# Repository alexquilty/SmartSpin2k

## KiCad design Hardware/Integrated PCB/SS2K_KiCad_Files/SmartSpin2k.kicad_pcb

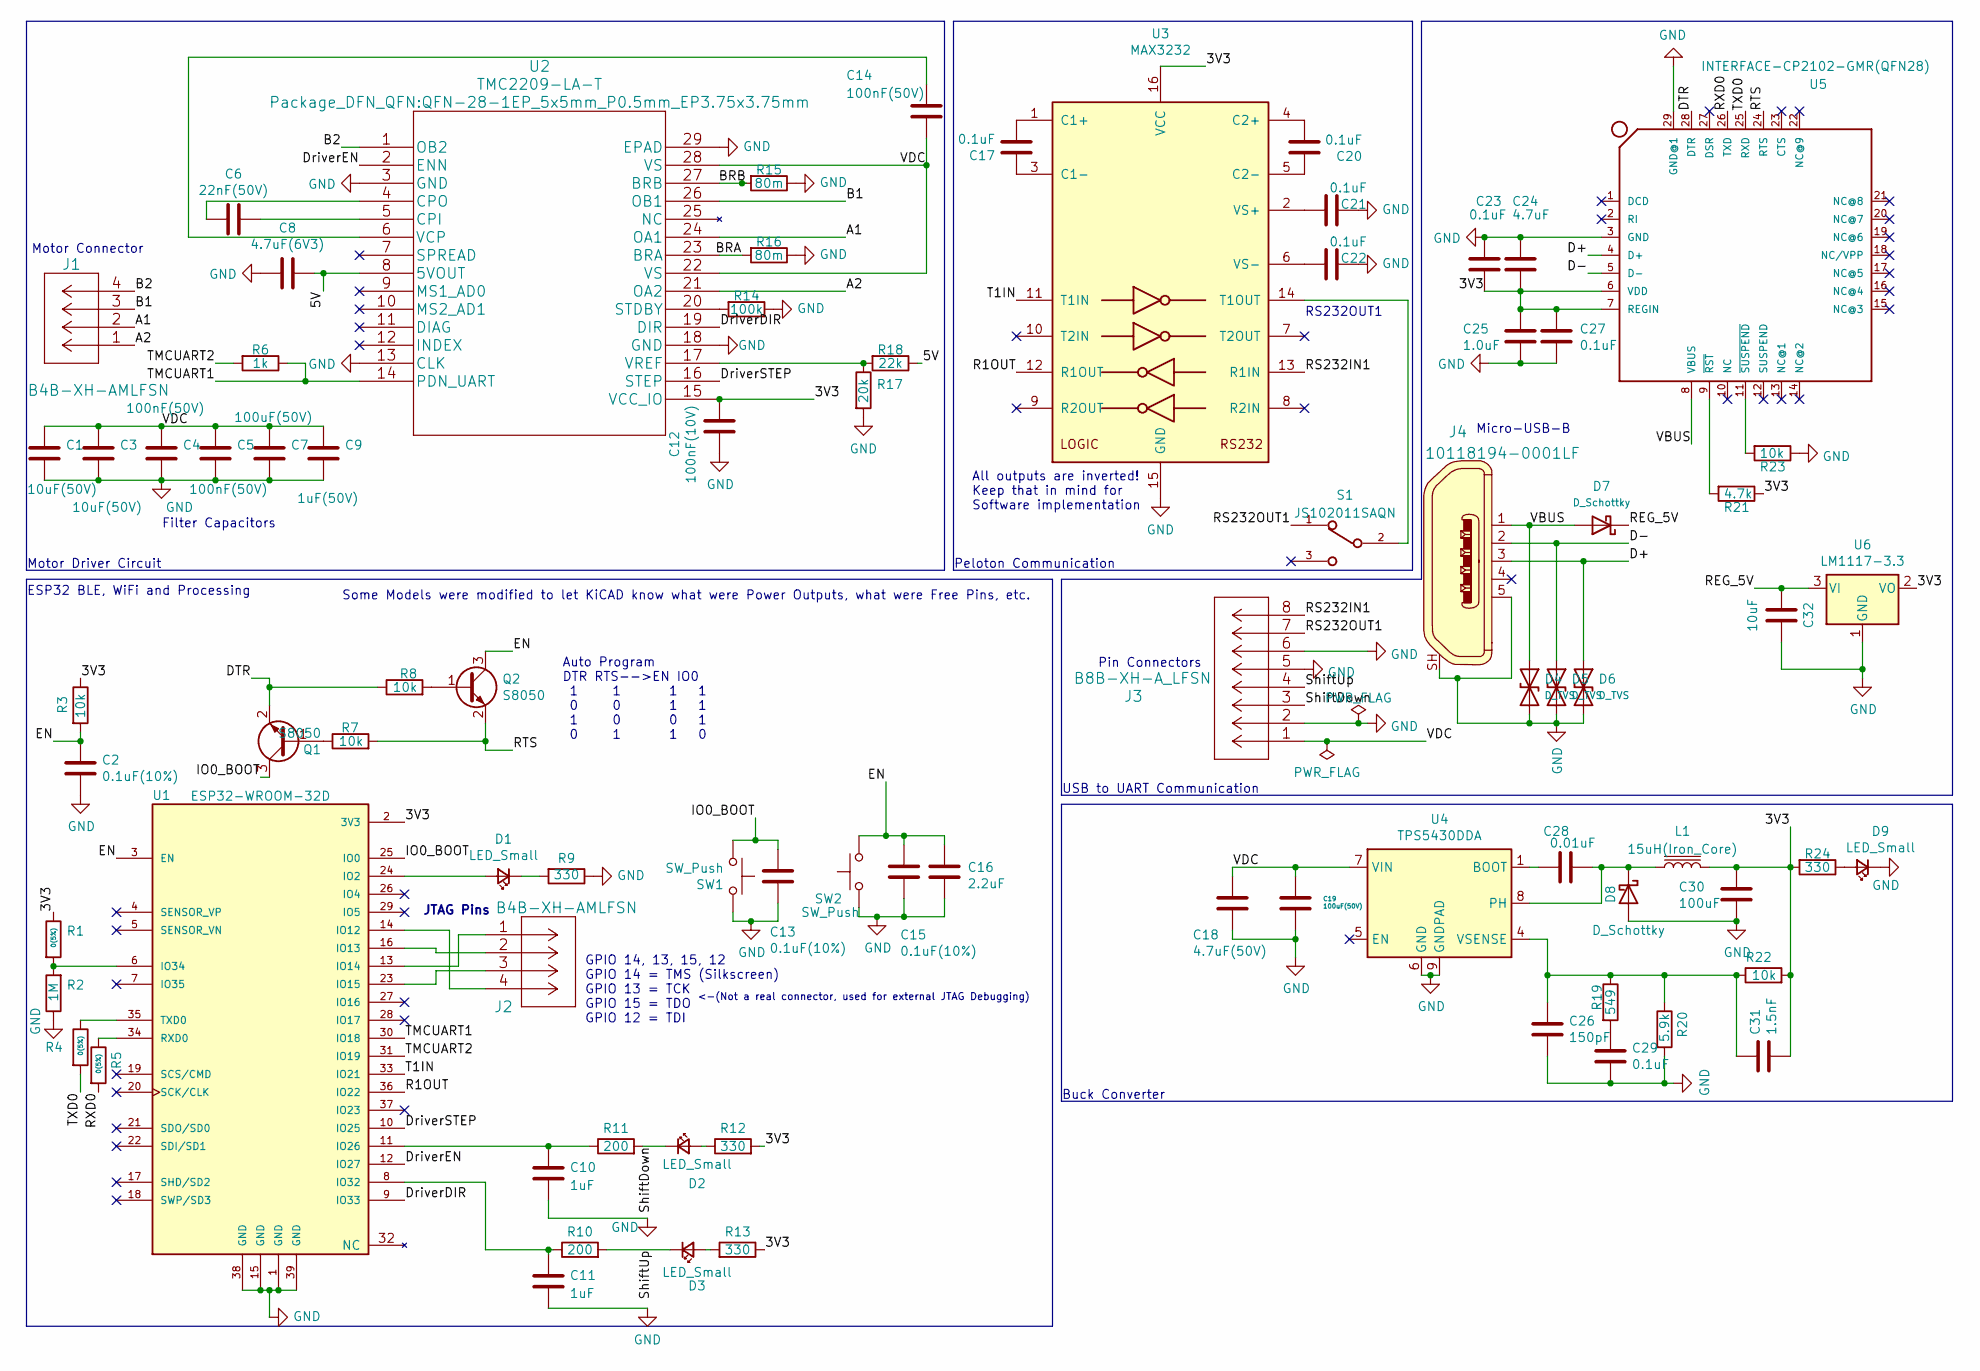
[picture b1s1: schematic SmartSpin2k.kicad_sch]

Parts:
C1: 10uF(50V); C_0805_2012Metric
C2, C13, C15: 0.1uF(10%); C_0402_1005Metric
C3: 10uF(50V); C_1206_3216Metric
C4, C5, C14: 100nF(50V); C_0805_2012Metric
C6: 22nF(50V); C_0805_2012Metric
C7, C19: 100uF(50V); CP_Elec_8x10
C8: 4.7uF(6V3); C_0805_2012Metric
C9: 1uF(50V); C_0603_1608Metric
C10, C11: 1uF; C_0603_1608Metric
C12: 100nF(10V); C_0805_2012Metric
C16: 2.2uF; C_0402_1005Metric
C17, C20, C21, C22, C23, C27, C29: 0.1uF; C_0402_1005Metric
C18: 4.7uF(50V); C_1206_3216Metric
C24: 4.7uF; C_0805_2012Metric
C25: 1.0uF; C_0805_2012Metric
C26: 150pF; C_0805_2012Metric
C28: 0.01uF; C_0805_2012Metric
C30: 100uF; C_1206_3216Metric
C31: 1.5nF; C_0805_2012Metric
C32: 10uF; C_0603_1608Metric
D1, D2, D3, D9: LED_Small; LED_0603_1608Metric
D4, D5, D6: D_TVS; D_0603_1608Metric
D7, D8: D_Schottky; D_SMA
J1, J2: B4B-XH-AMLFSN; JST_XH_B4B-XH-AM_1x04_P2.50mm_Vertical
J3: B8B-XH-A_LFSN; JST_XH_B8B-XH-AM_1x08_P2.50mm_Vertical
J4: 10118194-0001LF; USB_Micro_B_Female_10118194-0001LF; MPN 10118194-0001LF; Digi-Key_PN 609-4618-1-ND
L1: 15uH(Iron_Core); L_SXN_SMDRI127_150MT
Q1, Q2: S8050; SOT-23
R1, R4, R5: 0(5%); R_0402_1005Metric
R2: 1M; R_0402_1005Metric
R3, R7, R8, R22, R23: 10k; R_0402_1005Metric
R6: 1k; R_0402_1005Metric
R9, R12, R13, R24: 330; R_0402_1005Metric
R10, R11: 200; R_0402_1005Metric
R14: 100k; R_0402_1005Metric
R15, R16: 80m; R_1206_3216Metric
R17: 20k; R_0805_2012Metric
R18: 22k; R_0402_1005Metric
R19: 549; R_0402_1005Metric
R20: 5.9k; R_0603_1608Metric
R21: 4.7k; R_0402_1005Metric
S1: JS102011SAQN; SW_JS102011SAQN
SW1, SW2: SW_Push; SW_Push_SPST_NO_Alps_SKRK
U1: ESP32-WROOM-32D; ESP32-WROOM-32; PARTREV 1.9
U2: TMC2209-LA-T; QFN-28-1EP_5x5mm_P0.5mm_EP3.75x3.75mm
U3: MAX3232; MAX3232IPWR
U4: TPS5430DDA; SOIC-8-1EP_3.9x4.9mm_P1.27mm_EP2.514x3.2mm
U5: INTERFACE-CP2102-GMR(QFN28); QFN-28-1EP_5x5mm_P0.5mm_EP3.35x3.35mm; MPN CP2102-GMR
U6: LM1117-3.3; SOT-223-3_TabPin2

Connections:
/3V3: C12.1, C23.1, C24.2, C25.1, C27.1, C30.1, C31.2, L1.2, R1.1, R3.1, R12.2, R13.1, R21.1, R22.2, R24.2, U1.2 (3V3), U2.15 (VCC_IO), U3.16 (VCC), U5.6 (VDD), U5.7 (REGIN), U6.2 (VO)
/5V: C8.1, R18.1, U2.8 (5VOUT)
/A1: J1.2, U2.24 (OA1)
/A2: J1.1, U2.21 (OA2)
/B1: J1.3, U2.26 (OB1)
/B2: J1.4, U2.1 (OB2)
/BRA: R16.2, U2.23 (BRA)
/BRB: R15.2, U2.27 (BRB)
/D+: D6.1 (A1), J4.3, U5.4 (D+)
/D-: D5.1 (A1), J4.2, U5.5 (D-)
/DTR: Q1.2 (E), R8.1, U5.28 (DTR)
/DriverDIR: U1.9 (IO33), U2.19 (DIR)
/DriverEN: U1.12 (IO27), U2.2 (ENN)
/DriverSTEP: U1.10 (IO25), U2.16 (STEP)
/EN: C2.1, C15.1, C16.1, Q2.3 (C), R3.2, SW2.2, U1.3 (EN)
/IO0_BOOT: C13.1, Q1.3 (C), SW1.1, U1.25 (IO0)
/R1OUT: U1.36 (IO22), U3.12 (R1OUT)
/REG_5V: C32.2, D7.1 (K), U6.3 (VI)
/RS232IN1: J3.8, U3.13 (R1IN)
/RS232OUT1: J3.7, S1.1
/RTS: Q2.2 (E), R7.2, U5.24 (RTS)
/RXD0: R5.2, U5.26 (TXD)
/ShiftDown: D2.1 (K), J3.3, R11.2
/ShiftUp: D3.1 (K), J3.4, R10.2
/T1IN: U1.33 (IO21), U3.11 (T1IN)
/TMCUART1: R6.1, U1.30 (IO18), U2.14 (PDN_UART)
/TMCUART2: R6.2, U1.31 (IO19)
/TXD0: R4.2, U5.25 (RXD)
/VBUS: D4.1 (A1), D7.2 (A), J4.1, U5.8 (VBUS)
/VDC: C1.1, C3.1, C4.1, C5.1, C7.1, C9.1, C14.1, C18.1, C19.1, J3.1, U2.22 (VS), U2.28 (VS), U4.7 (VIN)
GND: C1.2, C2.2, C3.2, C4.2, C5.2, C7.2, C8.2, C9.2, C10.2, C11.2, C12.2, C13.2, C15.2, C16.2, C18.2, C19.2, C21.2, C22.2, C23.2, C24.1, C25.2, C26.2, C27.2, C29.2, C30.2, C32.1, D4.2 (A2), D5.2 (A2), D6.2 (A2), D8.2 (A), D9.1 (K), J3.2, J3.5, J3.6, J4.5, J4.SH, R2.1, R9.1, R14.1, R15.1, R16.1, R17.2, R20.2, R23.1, SW1.2, SW2.1, U1.1 (GND), U1.15 (GND), U1.38 (GND), U1.39 (GND), U2.3 (GND), U2.13 (CLK), U2.18 (GND), U2.29 (EPAD), U3.15 (GND), U4.6 (GND), U4.9 (GNDPAD), U5.3 (GND), U5.29 (GND@1), U6.1 (GND)
unnamed: C6.1, U2.5 (CPI)
unnamed: C6.2, U2.4 (CPO)
unnamed: C10.1, R11.1, U1.11 (IO26)
unnamed: C11.1, R10.1, U1.8 (IO32)
unnamed: C14.2, U2.6 (VCP)
unnamed: C17.1, U3.3 (C1-)
unnamed: C17.2, U3.1 (C1+)
unnamed: C20.1, U3.5 (C2-)
unnamed: C20.2, U3.4 (C2+)
unnamed: C21.1, U3.2 (VS+)
unnamed: C22.1, U3.6 (VS-)
unnamed: C26.1, C31.1, R19.1, R20.1, R22.1, U4.4 (VSENSE)
unnamed: C28.1, U4.1 (BOOT)
unnamed: C28.2, D8.1 (K), L1.1, U4.8 (PH)
unnamed: C29.1, R19.2
unnamed: D1.1 (K), R9.2
unnamed: D1.2 (A), U1.24 (IO2)
unnamed: D2.2 (A), R12.1
unnamed: D3.2 (A), R13.2
unnamed: D9.2 (A), R24.1
unnamed: J2.1, U1.13 (IO14)
unnamed: J2.2, U1.16 (IO13)
unnamed: J2.3, U1.23 (IO15)
unnamed: J2.4, U1.14 (IO12)
unnamed: Q1.1 (B), R7.1
unnamed: Q2.1 (B), R8.2
unnamed: R1.2, R2.2, U1.6 (IO34)
unnamed: R4.1, U1.35 (TXD0)
unnamed: R5.1, U1.34 (RXD0)
unnamed: R14.2, U2.20 (STDBY)
unnamed: R17.1, R18.2, U2.17 (VREF)
unnamed: R21.2, U5.9 (~RST)
unnamed: R23.2, U5.11 (~SUSPEND)
unnamed: S1.2, U3.14 (T1OUT)

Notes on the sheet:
Peloton Communication
JTAG Pins
Motor Connector
Buck Converter
ESP32 BLE, WiFi and Processing
RS232OUT1
USB to UART Communication
Pin Connectors
All outputs are inverted! Keep that in mind for Software implementation
<-(Not a real connector, used for external JTAG Debugging)
Some Models were modified to let KiCAD know what were Power Outputs, what were Free Pins, etc.
Auto Program DTR RTS-->EN IO0 1 1 1 1 0 0 1 1 1 0 0 1 0 1 1 0
GPIO 14, 13, 15, 12 GPIO 14 = TMS (Silkscreen) GPIO 13 = TCK GPIO 15 = TDO GPIO 12 = TDI
Motor Driver Circuit
Filter Capacitors
Micro-USB-B

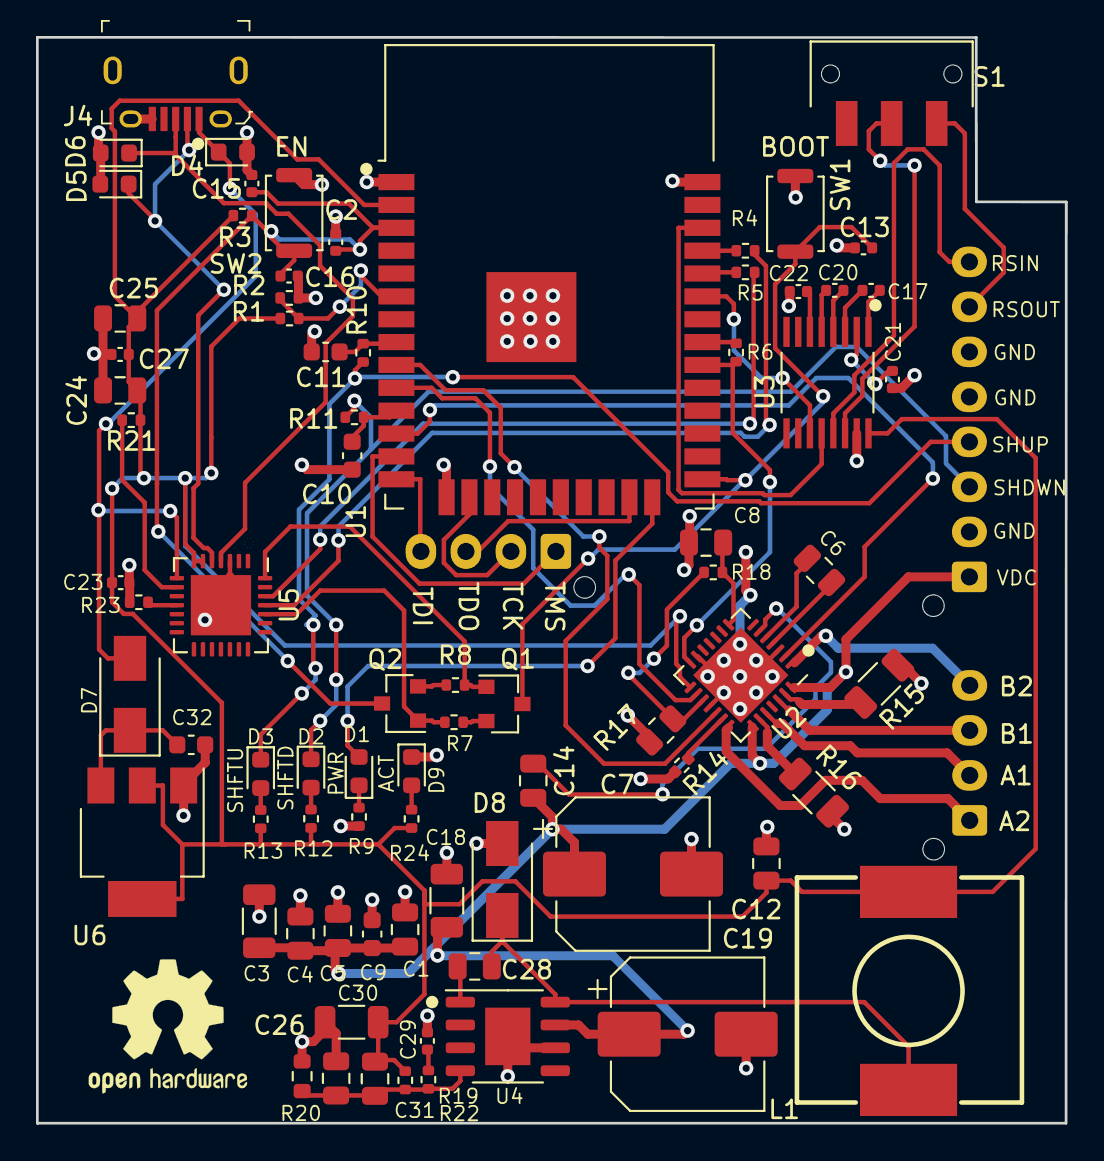
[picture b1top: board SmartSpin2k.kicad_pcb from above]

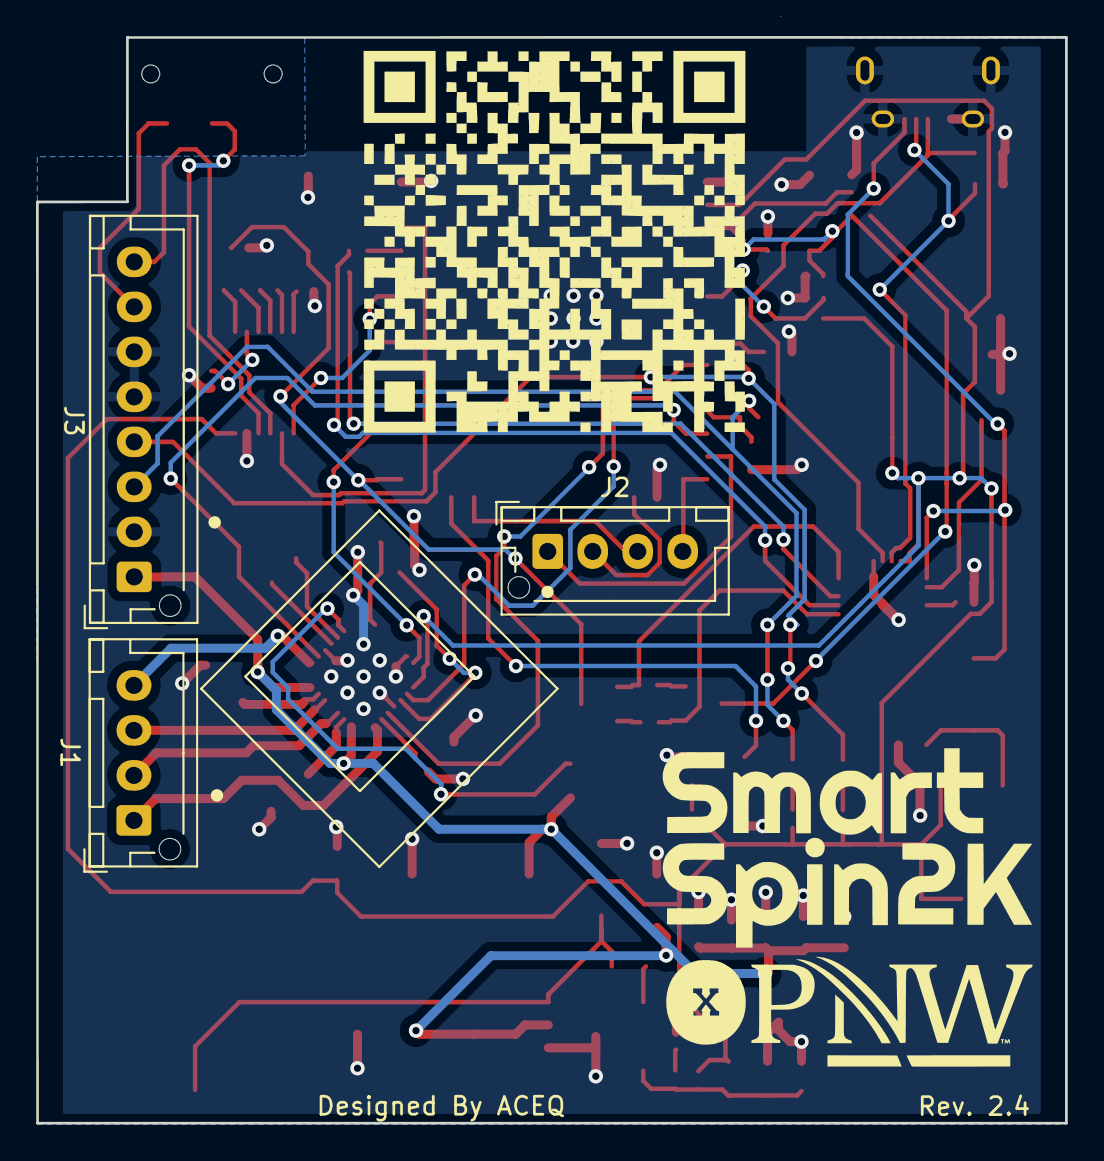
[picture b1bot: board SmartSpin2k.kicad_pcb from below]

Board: 2 copper layers, 57.2 x 60.3 mm, 81 parts (3 on the bottom side), 65 nets.

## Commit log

2022-10-20 Power Buffer Troubleshooting
    Added PowerBuffer to toLog().
2022-12-04 New Board Changes to Switch and Edges

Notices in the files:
parts and their libraries:
Copyright 2021 Accelerated Designs. All rights reserved.
